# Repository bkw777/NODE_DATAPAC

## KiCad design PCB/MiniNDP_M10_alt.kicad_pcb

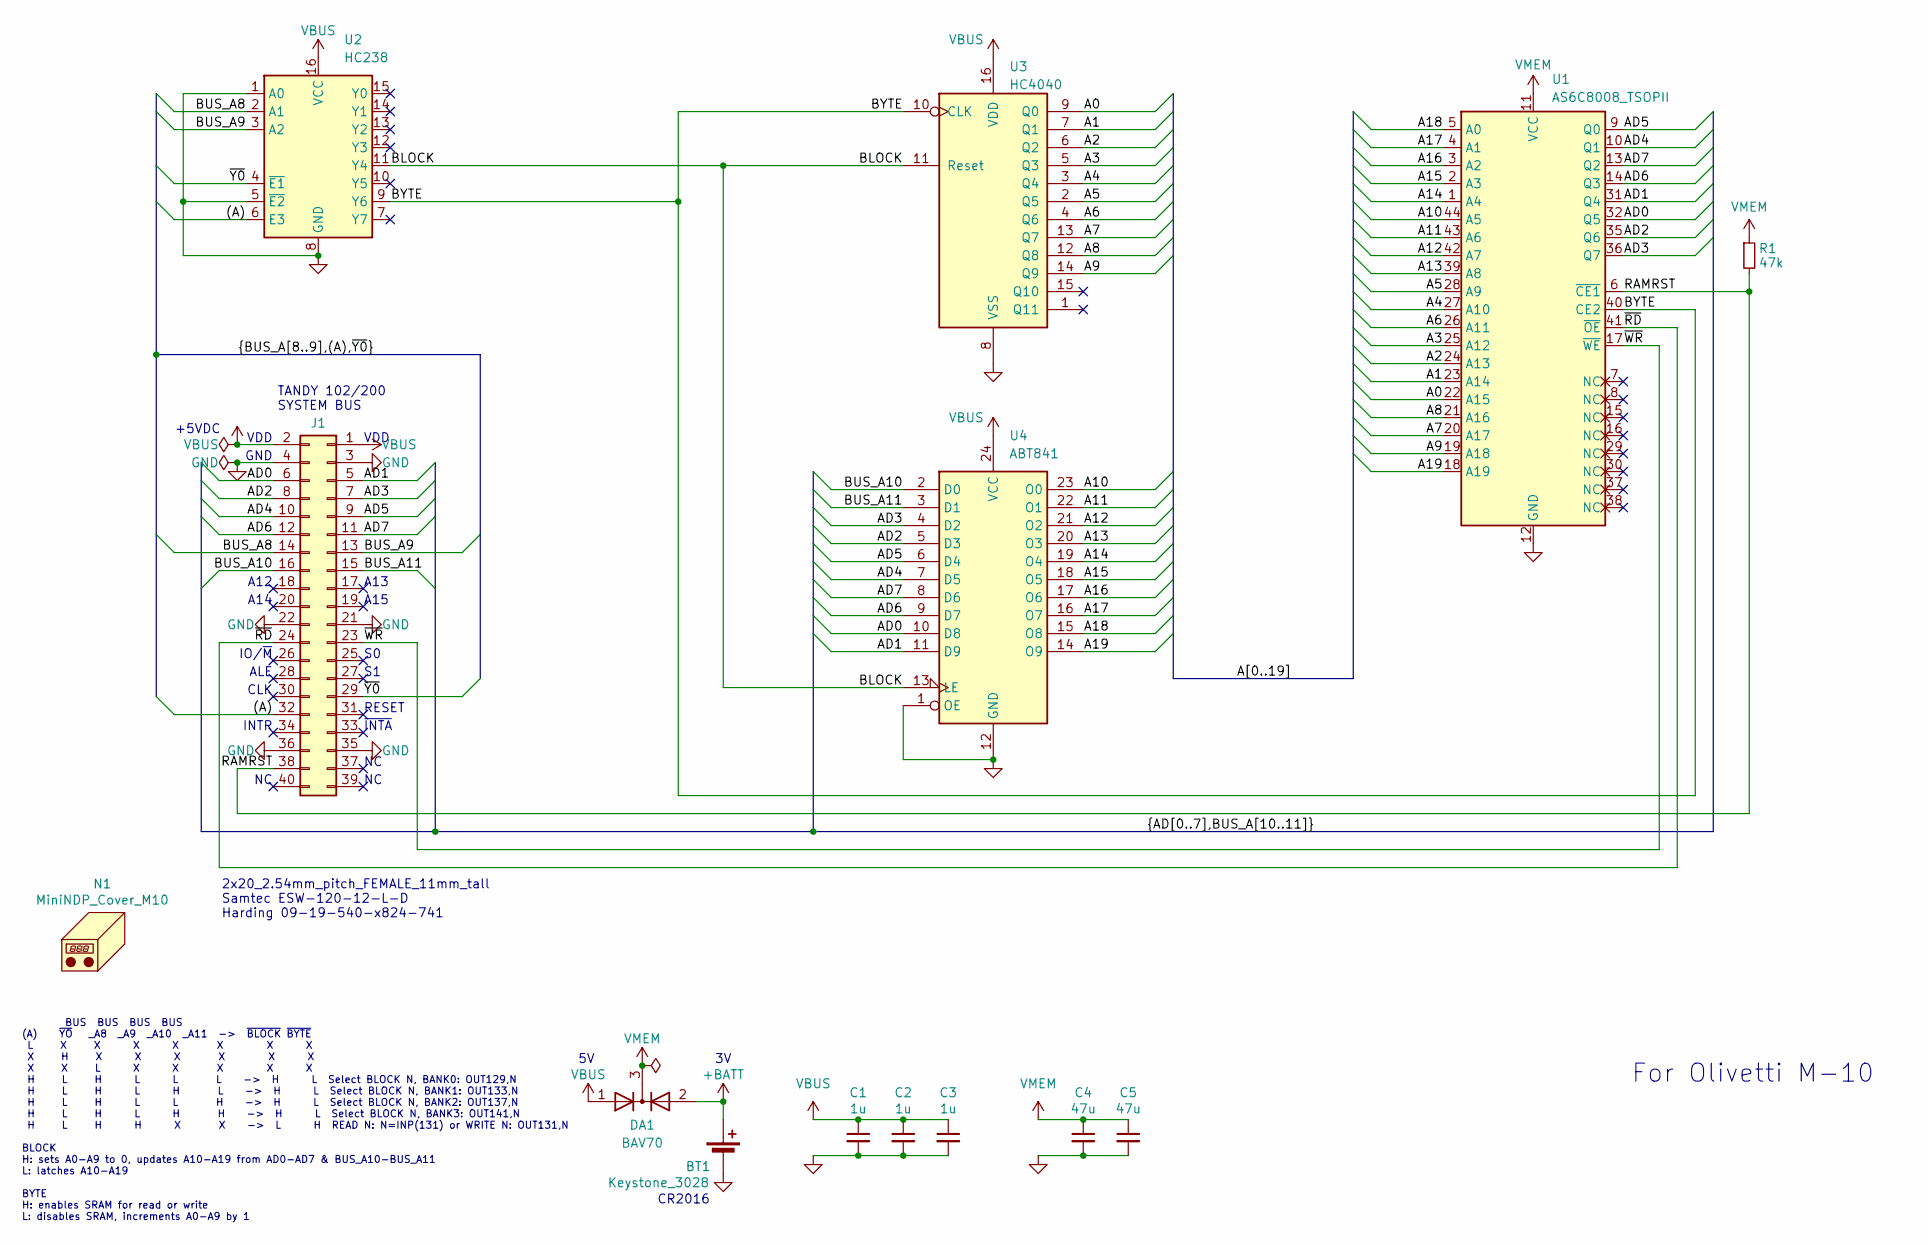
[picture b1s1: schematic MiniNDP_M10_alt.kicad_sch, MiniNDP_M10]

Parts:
BT1: Keystone_3028; Keystone_3028_3034; MPN Keystone 3028
C1, C2, C3: 1u; C_0805; MPN CL21B105KAFNNNE
C4, C5: 47u; C_1206; MPN C3216X5R1E476M160DC
DA1: BAV70; SOT-23; MPN BAV70-7-F
J1: Conn_02x20_Odd_Even; Harding_09-19-540-x824-741; MPN 09195407824741
N1: MiniNDP_Cover_M10; MiniNDP_Cover_THIN; MPN MiniNDP_Cover_THIN.stl
R1: 47k; R_0805; MPN RMCF0805FT47K0
U1: AS6C8008_TSOPII; TSOP-II-44; MPN AS6C8008-55ZIN
U2: HC238; TSSOP-16; MPN 74HC238PW,118
U3: HC4040; TSSOP-16; MPN 74HC4040PW,118
U4: ABT841; TSSOP-24_4.4x7.8mm_P0.65mm; MPN SN74ABT841APW

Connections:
+BATT: BT1.1 (+), DA1.2 (A)
/(A): J1.32, U2.6 (E3)
/A0: U1.22 (A15), U3.9 (Q0)
/A1: U1.23 (A14), U3.7 (Q1)
/A2: U1.24 (A13), U3.6 (Q2)
/A3: U1.25 (A12), U3.5 (Q3)
/A4: U1.27 (A10), U3.3 (Q4)
/A5: U1.28 (A9), U3.2 (Q5)
/A6: U1.26 (A11), U3.4 (Q6)
/A7: U1.20 (A17), U3.13 (Q7)
/A8: U1.21 (A16), U3.12 (Q8)
/A9: U1.19 (A18), U3.14 (Q9)
/A10: U1.44 (A5), U4.23 (O0)
/A11: U1.43 (A6), U4.22 (O1)
/A12: U1.42 (A7), U4.21 (O2)
/A13: U1.39 (A8), U4.20 (O3)
/A14: U1.1 (A4), U4.19 (O4)
/A15: U1.2 (A3), U4.18 (O5)
/A16: U1.3 (A2), U4.17 (O6)
/A17: U1.4 (A1), U4.16 (O7)
/A18: U1.5 (A0), U4.15 (O8)
/A19: U1.18 (A19), U4.14 (O9)
/AD0: J1.6, U1.32 (Q5), U4.10 (D8)
/AD1: J1.5, U1.31 (Q4), U4.11 (D9)
/AD2: J1.8, U1.35 (Q6), U4.5 (D3)
/AD3: J1.7, U1.36 (Q7), U4.4 (D2)
/AD4: J1.10, U1.10 (Q1), U4.7 (D5)
/AD5: J1.9, U1.9 (Q0), U4.6 (D4)
/AD6: J1.12, U1.14 (Q3), U4.9 (D7)
/AD7: J1.11, U1.13 (Q2), U4.8 (D6)
/BLOCK: U2.11 (Y4), U3.11 (Reset), U4.13 (LE)
/BUS_A8: J1.14, U2.2 (A1)
/BUS_A9: J1.13, U2.3 (A2)
/BUS_A10: J1.16, U4.2 (D0)
/BUS_A11: J1.15, U4.3 (D1)
/BYTE: U1.40 (CE2), U2.9 (Y6), U3.10 (CLK)
/RAMRST: J1.38, R1.2, U1.6 (~CE1)
/~RD: J1.24, U1.41 (~OE)
/~WR: J1.23, U1.17 (~WE)
/~Y0: J1.29, U2.4 (~E1)
GND: BT1.2 (-), C1.2, C2.2, C3.2, C4.2, C5.2, J1.3, J1.4, J1.21, J1.22, J1.35, J1.36, U1.12 (GND), U1.34 (GND), U2.1 (A0), U2.5 (~E2), U2.8 (GND), U3.8 (VSS), U4.1 (OE), U4.12 (GND)
VBUS: C1.1, C2.1, C3.1, DA1.1 (A), J1.1, J1.2, U2.16 (VCC), U3.16 (VDD), U4.24 (VCC)
VMEM: C4.1, C5.1, DA1.3 (K), R1.1, U1.11 (VCC), U1.33 (VCC)

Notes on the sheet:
TANDY 102/200 SYSTEM BUS
+5VDC
A15
CR2016
INTR
A14
ALE
~{INTA}
CLK
GND
IO/~{M}
VDD
BUS BUS BUS BUS (A) ~{YO} _A8 _A9 _A10 _A11 -> ~{BLOCK} ~{BYTE} L X X X X X X X X H X X X X X X X X L X X X X X H L H L L L -> H L Select BLOCK N, BANK0: OUT129,N H L H L H L -> H L Select BLOCK N, BANK1: OUT133,N H L H L L H -> H L Select BLOCK N, BANK2: OUT137,N H L H L H H -> H L Select BLOCK N,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
2x20_2.54mm_pitch_FEMALE_11mm_tall Samtec ESW-120-12-L-D Harding 09-19-540-x824-741
RESET
A13
A12
For Olivetti M-10

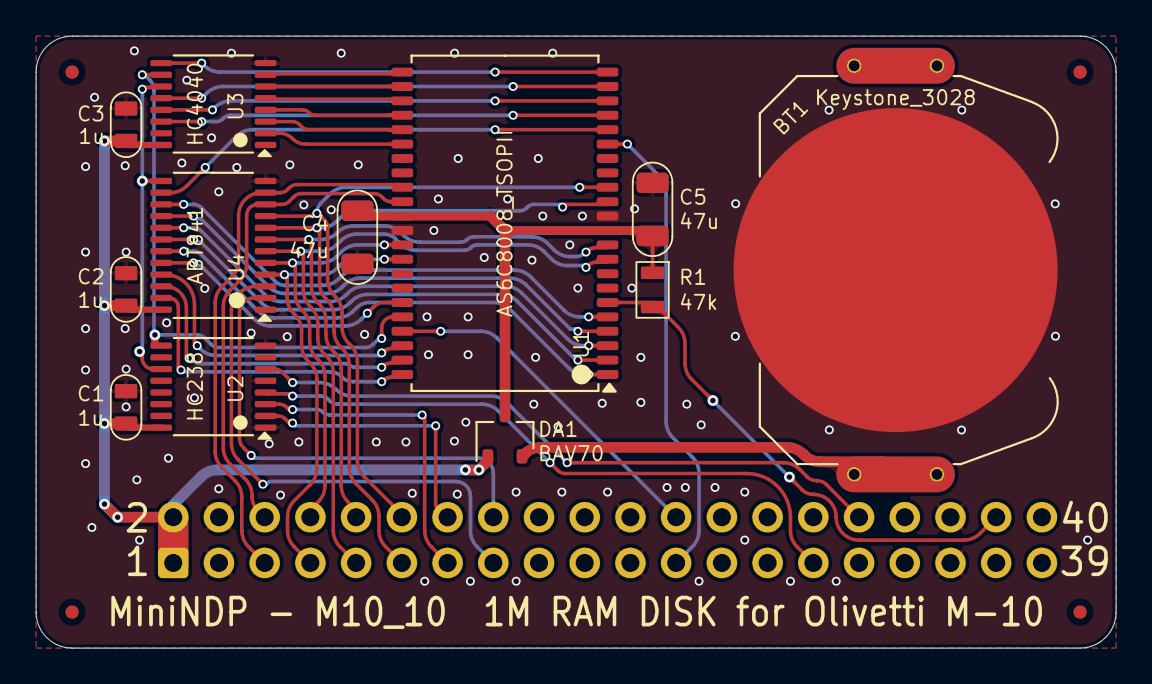
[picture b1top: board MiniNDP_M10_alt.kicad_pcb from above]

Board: 2 copper layers, 60.0 x 34.0 mm, 18 parts (1 on the bottom side), 43 nets.

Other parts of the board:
F3, F3#2, F3#3, F3#4: Fiducial_0.75_1.5

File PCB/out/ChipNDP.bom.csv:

"Reference","Value","Datasheet","Footprint","Qty","DNP","MPN","Description"
"BT1","Keystone_3031","datasheet/Keystone_3031.pdf","000_LOCAL:Keystone_3031","1","","Keystone 3031","Battery Retainer Coin, 10.0mm 1 Cell PC Pin"
"C1,C2,C3","1u","datasheets/CL21B105KAFNNNE.pdf","000_LOCAL:C_0805","3","","CL21B105KAFNNNE","CAP CER 1UF 25V X7R 0805"
"C4","47u","datasheets/TDK_MLCC_Cxxxx.pdf","000_LOCAL:C_1206","1","","C3216X5R1E476M160DC","CAP CER 47UF 25V X5R 1206"
"DA1","BAV70","datasheets/BAV70.pdf","000_LOCAL:SOT-23","1","","BAV70-7-F","DIODE ARRAY GP 75V 150MA SOT23-3"
"J1","Model_100_System_BUS","datasheets/TRS-80_Model_100_User_Guide.pdf","000_LOCAL:DIP-40_PCB","1","","920-0172-01","CONN HEADER VERT 40P 2.54MM"
"R1","47k","datasheets/sei-rmcf_rmcp.pdf","000_LOCAL:R_0805","1","","RMCF0805FT47K0","RES 47K OHM 1% 1/8W 0805"
"U1","AS6C8008_TSOPII","datasheets/AS6C8008.pdf","000_LOCAL:TSOP-II-44","1","","AS6C8008-55ZIN","IC SRAM 1Mx8 PARALLEL 5v TSOP-II-44"
"U2","HC238","datasheets/HC238.pdf","000_LOCAL:TSSOP-16","1","","74HC238PW,118","IC DECODER/DEMUX 1 X 3:8 16SO"
"U3","HC4040","datasheets/4040.pdf","000_LOCAL:TSSOP-16","1","","74HC4040PW,118","IC BINARY COUNTER 12-BIT 16SO"
"U4","ABT841","datasheets/sn54abt841.pdf","000_LOCAL:TSSOP-24_4.4x7.8mm_P0.65mm","1","","SN74ABT841APW","IC 10BIT LATCH 3-STATE 24-SOIC"

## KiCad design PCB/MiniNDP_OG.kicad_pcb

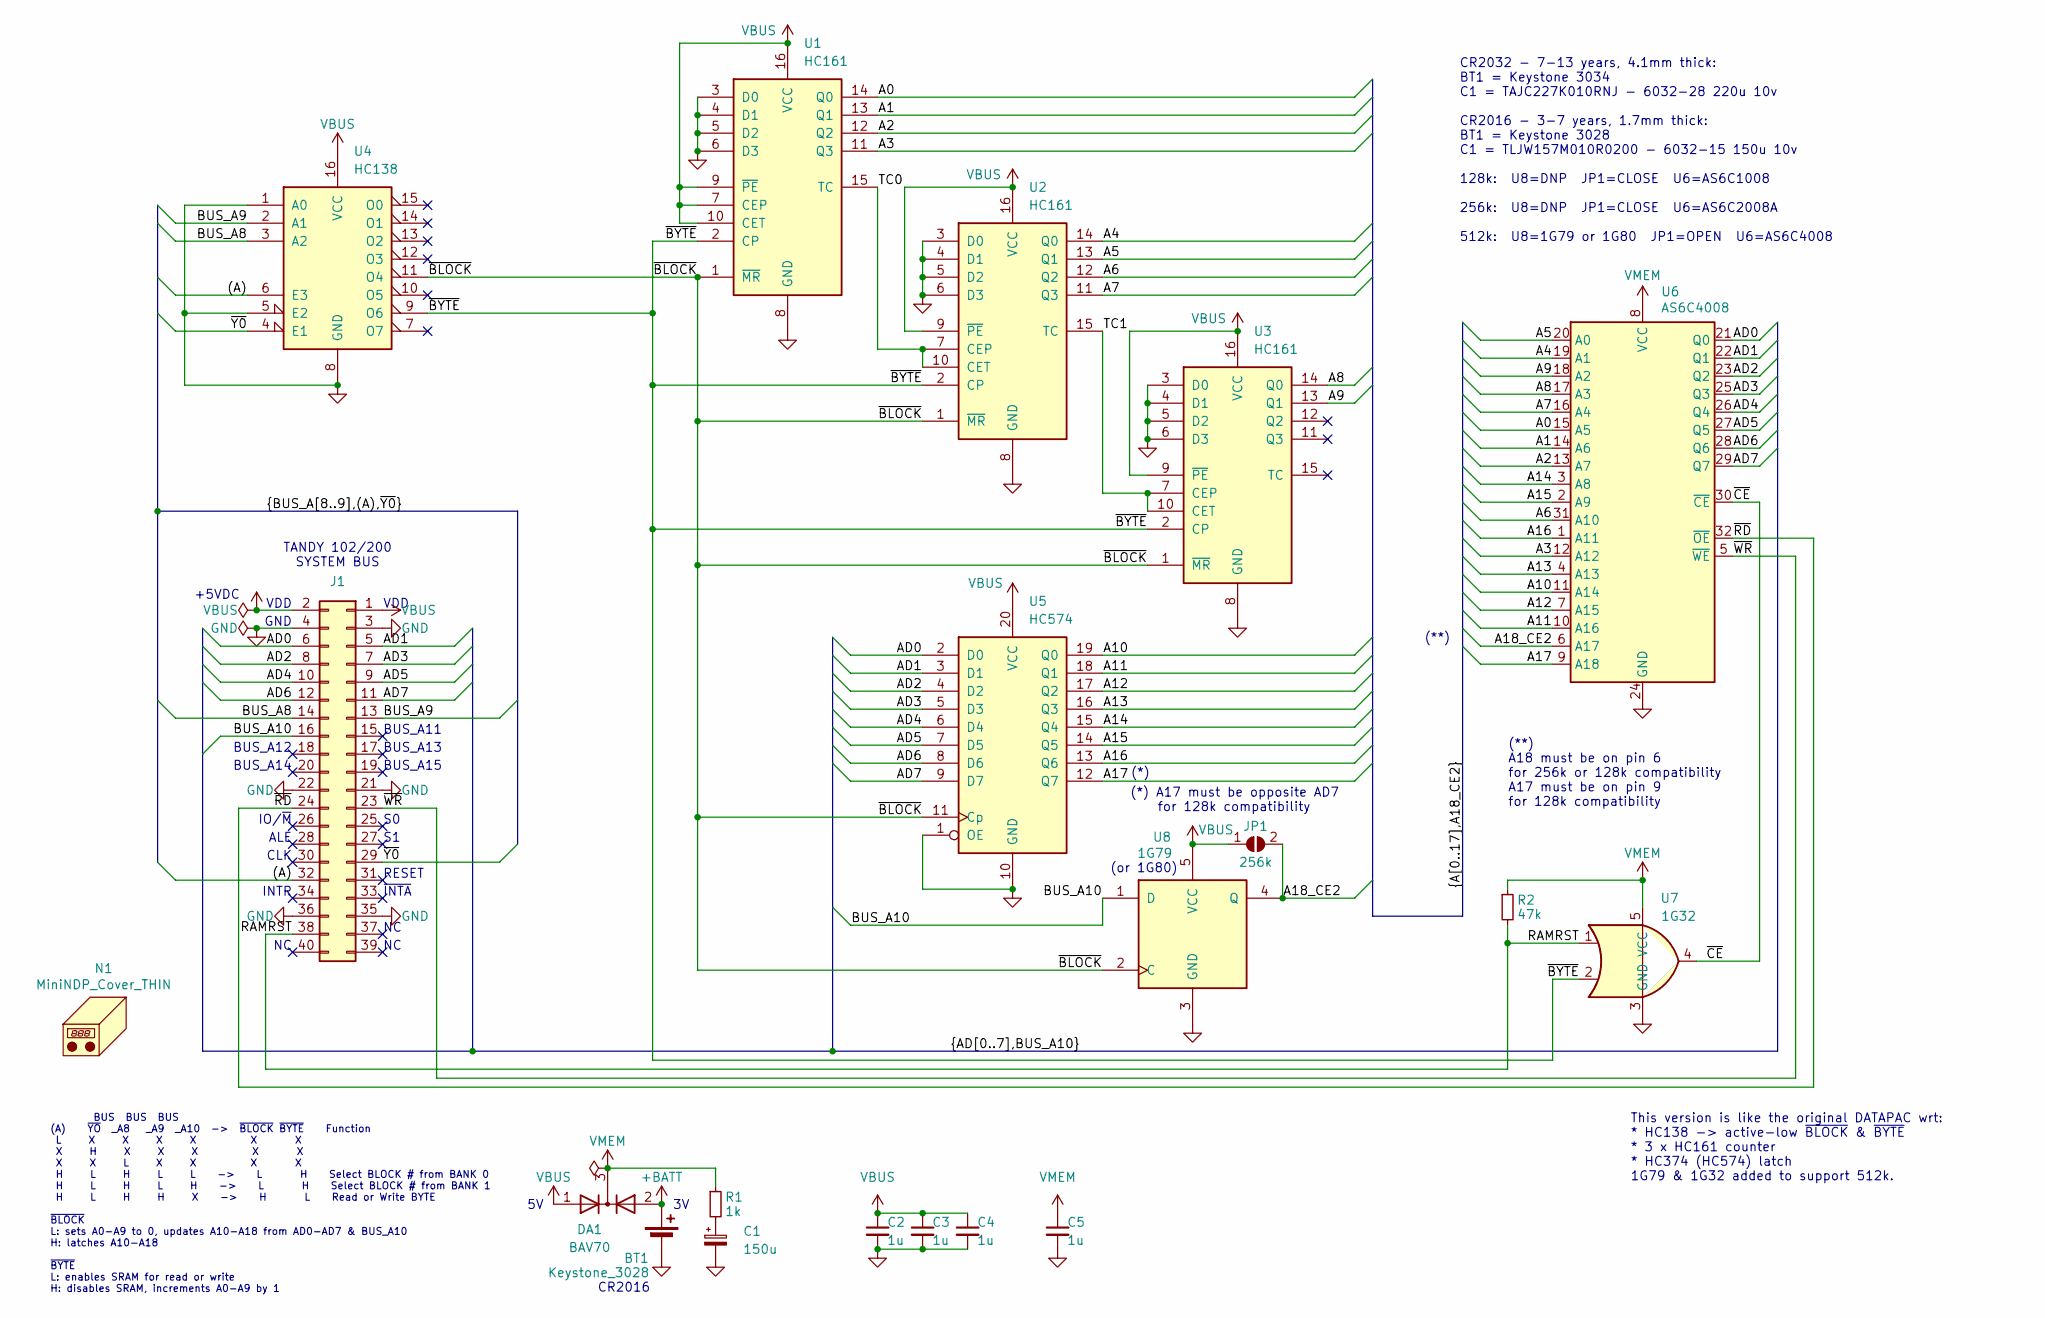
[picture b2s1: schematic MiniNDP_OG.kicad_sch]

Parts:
BT1: Keystone_3028; Keystone_3028_3034; MPN Keystone_3028
C1: 150u; CP_6032; MPN TLJW157M010R0200
C2, C3, C4, C5: 1u; C_0805; MPN CL21B105KAFNNNE
DA1: BAV70; SOT-23; MPN BAV70-7-F
J1: Conn_02x20_Odd_Even; IDC-Header_2x20_P2.54mm_Vertical; MPN 302-S401
JP1: 256k; SolderJumper-2_Open 0.65mm
N1: MiniNDP_Cover_THIN; MPN MiniNDP_Cover_THIN.stl
R1: 1k; R_0805; MPN RK73B2ATTD102J
R2: 47k; R_0805; MPN RMCF0805FT47K0
U1, U2, U3: HC161; TSSOP-16; MPN 74HC161PW,118
U4: HC138; TSSOP-16; MPN 74HC138PW,118
U5: HC574; TSSOP-20; MPN 74HC574PW,118
U6: AS6C4008; TSOP32-dual; MPN AS6C4008-55STIN
U7: 1G32; SOT-353_SC-70-5; MPN 74LVC1G32GW,125
U8: 1G79; SOT-353_SC-70-5; MPN 74LVC1G79GW,125

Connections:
+BATT: BT1.1 (+), DA1.2 (A)
/(A): J1.32, U4.6 (E3)
/A0: U1.14 (Q0), U6.15 (A5)
/A1: U1.13 (Q1), U6.14 (A6)
/A2: U1.12 (Q2), U6.13 (A7)
/A3: U1.11 (Q3), U6.12 (A12)
/A4: U2.14 (Q0), U6.19 (A1)
/A5: U2.13 (Q1), U6.20 (A0)
/A6: U2.12 (Q2), U6.31 (A10)
/A7: U2.11 (Q3), U6.16 (A4)
/A8: U3.14 (Q0), U6.17 (A3)
/A9: U3.13 (Q1), U6.18 (A2)
/A10: U5.19 (Q0), U6.11 (A14)
/A11: U5.18 (Q1), U6.10 (A16)
/A12: U5.17 (Q2), U6.7 (A15)
/A13: U5.16 (Q3), U6.4 (A13)
/A14: U5.15 (Q4), U6.3 (A8)
/A15: U5.14 (Q5), U6.2 (A9)
/A16: U5.13 (Q6), U6.1 (A11)
/A17: U5.12 (Q7), U6.9 (A18)
/A18_CE2: JP1.2 (B), U6.6 (A17), U8.4 (Q)
/AD0: J1.6, U5.2 (D0), U6.21 (Q0)
/AD1: J1.5, U5.3 (D1), U6.22 (Q1)
/AD2: J1.8, U5.4 (D2), U6.23 (Q2)
/AD3: J1.7, U5.5 (D3), U6.25 (Q3)
/AD4: J1.10, U5.6 (D4), U6.26 (Q4)
/AD5: J1.9, U5.7 (D5), U6.27 (Q5)
/AD6: J1.12, U5.8 (D6), U6.28 (Q6)
/AD7: J1.11, U5.9 (D7), U6.29 (Q7)
/BUS_A8: J1.14, U4.3 (A2)
/BUS_A9: J1.13, U4.2 (A1)
/BUS_A10: J1.16, U8.1 (D)
/RAMRST: J1.38, R2.2, U7.1
/TC0: U1.15 (TC), U2.7 (CEP), U2.10 (CET)
/TC1: U2.15 (TC), U3.7 (CEP), U3.10 (CET)
/~BLOCK: U1.1 (~MR), U2.1 (~MR), U3.1 (~MR), U4.11 (O4), U5.11 (Cp), U8.2 (C)
/~BYTE: U1.2 (CP), U2.2 (CP), U3.2 (CP), U4.9 (O6), U7.2
/~CE: U6.30 (~CE), U7.4
/~RD: J1.24, U6.32 (~OE)
/~WR: J1.23, U6.5 (~WE)
/~Y0: J1.29, U4.4 (E1)
GND: BT1.2 (-), C1.2, C2.2, C3.2, C4.2, C5.2, J1.3, J1.4, J1.21, J1.22, J1.35, J1.36, U1.3 (D0), U1.4 (D1), U1.5 (D2), U1.6 (D3), U1.8 (GND), U2.3 (D0), U2.4 (D1), U2.5 (D2), U2.6 (D3), U2.8 (GND), U3.3 (D0), U3.4 (D1), U3.5 (D2), U3.6 (D3), U3.8 (GND), U4.1 (A0), U4.5 (E2), U4.8 (GND), U5.1 (OE), U5.10 (GND), U6.24 (GND), U7.3 (GND), U8.3 (GND)
unnamed: C1.1, R1.2
VBUS: C2.1, C3.1, C4.1, DA1.1 (A), J1.1, J1.2, JP1.1 (A), U1.7 (CEP), U1.9 (~PE), U1.10 (CET), U1.16 (VCC), U2.9 (~PE), U2.16 (VCC), U3.9 (~PE), U3.16 (VCC), U4.16 (VCC), U5.20 (VCC), U8.5 (VCC)
VMEM: C5.1, DA1.3 (K), R1.1, R2.1, U6.8 (VCC), U7.5 (VCC)

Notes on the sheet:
TANDY 102/200 SYSTEM BUS
+5VDC
BUS_A15
INTR
BUS_A14
ALE
~{INTA}
CLK
(**) A18 must be on pin 6 for 256k or 128k compatibility A17 must be on pin 9 for 128k compatibility
CR2032 - 7-13 years, 4.1mm thick: BT1 = Keystone 3034 C1 = TAJC227K010RNJ - 6032-28 220u 10v CR2016 - 3-7 years, 1.7mm thick: BT1 = Keystone 3028 C1 = TLJW157M010R0200 - 6032-15 150u 10v 128k: U8=DNP JP1=CLOSE U6=AS6C1008 256k: U8=DNP JP1=CLOSE U6=AS6C2008A 512k: U8=1G79 or 1G80 JP1=OPEN U6=AS6C4008
GND
IO/~{M}
CR2016
(or 1G80)
VDD
BUS BUS BUS (A) ~{YO} _A8 _A9 _A10 -> ~{BLOCK} ~{BYTE} Function L X X X X X X X H X X X X X X X L X X X X H L H L L -> L H Select BLOCK # from BANK 0 H L H L H -> L H Select BLOCK # from BANK 1 H L H H X -> H L Read or Write BYTE ~{BLOCK} L: sets A0-A9 to 0, updates A10-A18 from AD0-AD7 & BUS_A10 H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
RESET
(*) A17 must be opposite AD7 for 128k compatibility
This version is like the original DATAPAC wrt: * HC138 -> active-low ~{BLOCK} & ~{BYTE} * 3 x HC161 counter * HC374 (HC574) latch 1G79 & 1G32 added to support 512k.
(**)
BUS_A11
BUS_A13
(*)
BUS_A12

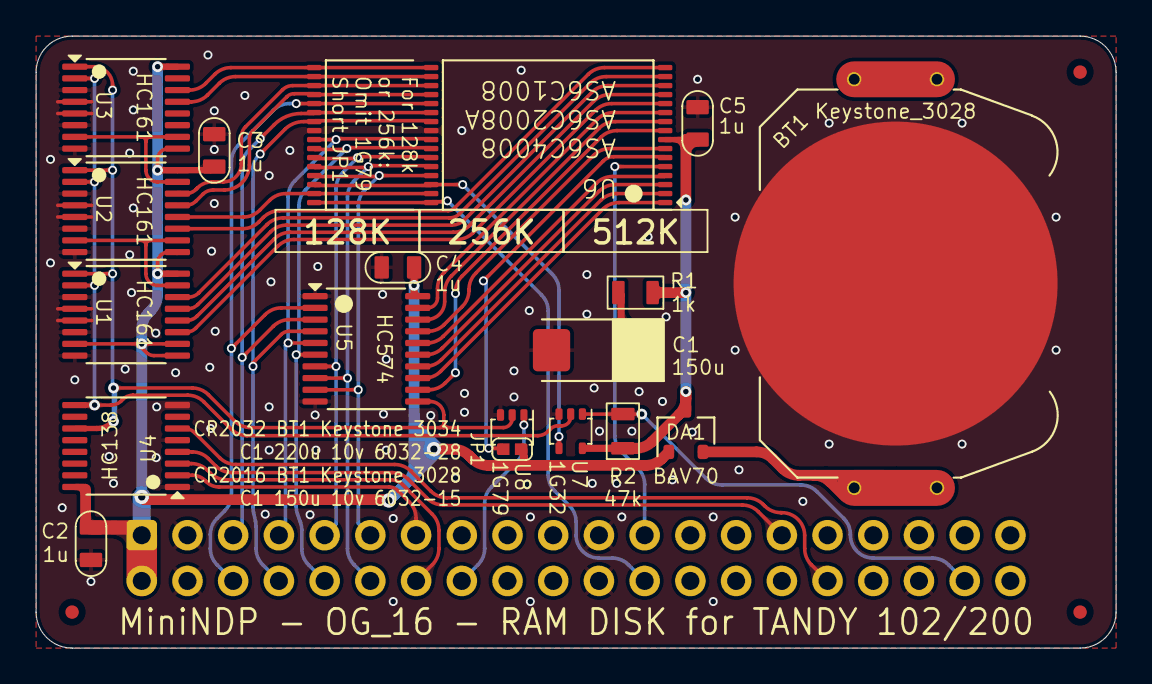
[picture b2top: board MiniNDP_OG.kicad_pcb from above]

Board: 2 copper layers, 60.0 x 34.0 mm, 23 parts (1 on the bottom side), 45 nets.

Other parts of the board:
F3, F3#2, F3#3: Fiducial_0.75_1.5

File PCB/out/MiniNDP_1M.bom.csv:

"Reference","Value","Datasheet","Footprint","Qty","DNP","MPN","Description"
"BT1","Keystone_3034","datasheets/Keystone_3034.pdf","000_LOCAL:Keystone_3028_3034","1","","Keystone 3034","SMT 20mm x 3.2mm coin cell holder"
"C1","220u10v","datasheets/TAJ.odf","000_LOCAL:CP_6032","1","","TAJC227K010RNJ","CAP TANT 220UF 10% 10V 2312"
"C2,C3,C4,C5","1u","datasheets/CL21B105KAFNNNE.pdf","000_LOCAL:C_0805","4","","CL21B105KAFNNNE","CAP CER 1UF 25V X7R 0805"
"DA1","BAS70DW-05","datasheets/BAS70.pdf","000_LOCAL:SOT-363_SC-70-6_symmetric","1","","BAS70DW-05-7-F","DIODE ARR SCHOTT 70V 70MA SOT363 2-PAIR COMMON-CATHODE"
"J1","Conn_02x20_Odd_Even","datasheets/2x20_male_boxed.pdf","000_LOCAL:IDC-Header_2x20_P2.54mm_Vertical","1","","302-S401","CONN HEADER VERT 40POS 2.54MM"
"R1","1k","datasheets/RK73.pdf","000_LOCAL:R_0805","1","","RK73B2ATTD102J","RES 1K OHM 5% 1/4W 0805"
"R2","47k","datasheets/sei-rmcf_rmcp.pdf","000_LOCAL:R_0805","1","","RMCF0805FT47K0","RES 47K OHM 1% 1/8W 0805"
"U1,U2,U3","HC161","datasheets/HC161.pdf","000_LOCAL:TSSOP-16","3","","74HC161PW,118","IC BINARY COUNTER 4-BIT 16TSSOP"
"U4","HC138","datasheets/HC138.pdf","000_LOCAL:TSSOP-16","1","","74HC138PW,118","IC DECODER/DEMUX 1X3:8 16TSSOP"
"U5","FCT821","datasheets/CY74FCT821T.pdf","000_LOCAL:SOIC-24","1","","CY74FCT821BTSOC","IC FF D-TYPE SNGL 10BIT 24SOIC"
"U6","AS6C8008_TSOPII","datasheets/AS6C8008.pdf","000_LOCAL:TSOP-II-44","1","","AS6C8008-55ZIN","IC SRAM 1Mx8 PARALLEL 5v TSOP-II-44"
"U7","1G32","datasheets/LVC1G32.pdf","000_LOCAL:SOT-353_SC-70-5","1","","74LVC1G32GW,125","IC GATE OR 1CH 2-INP 5TSSOP"

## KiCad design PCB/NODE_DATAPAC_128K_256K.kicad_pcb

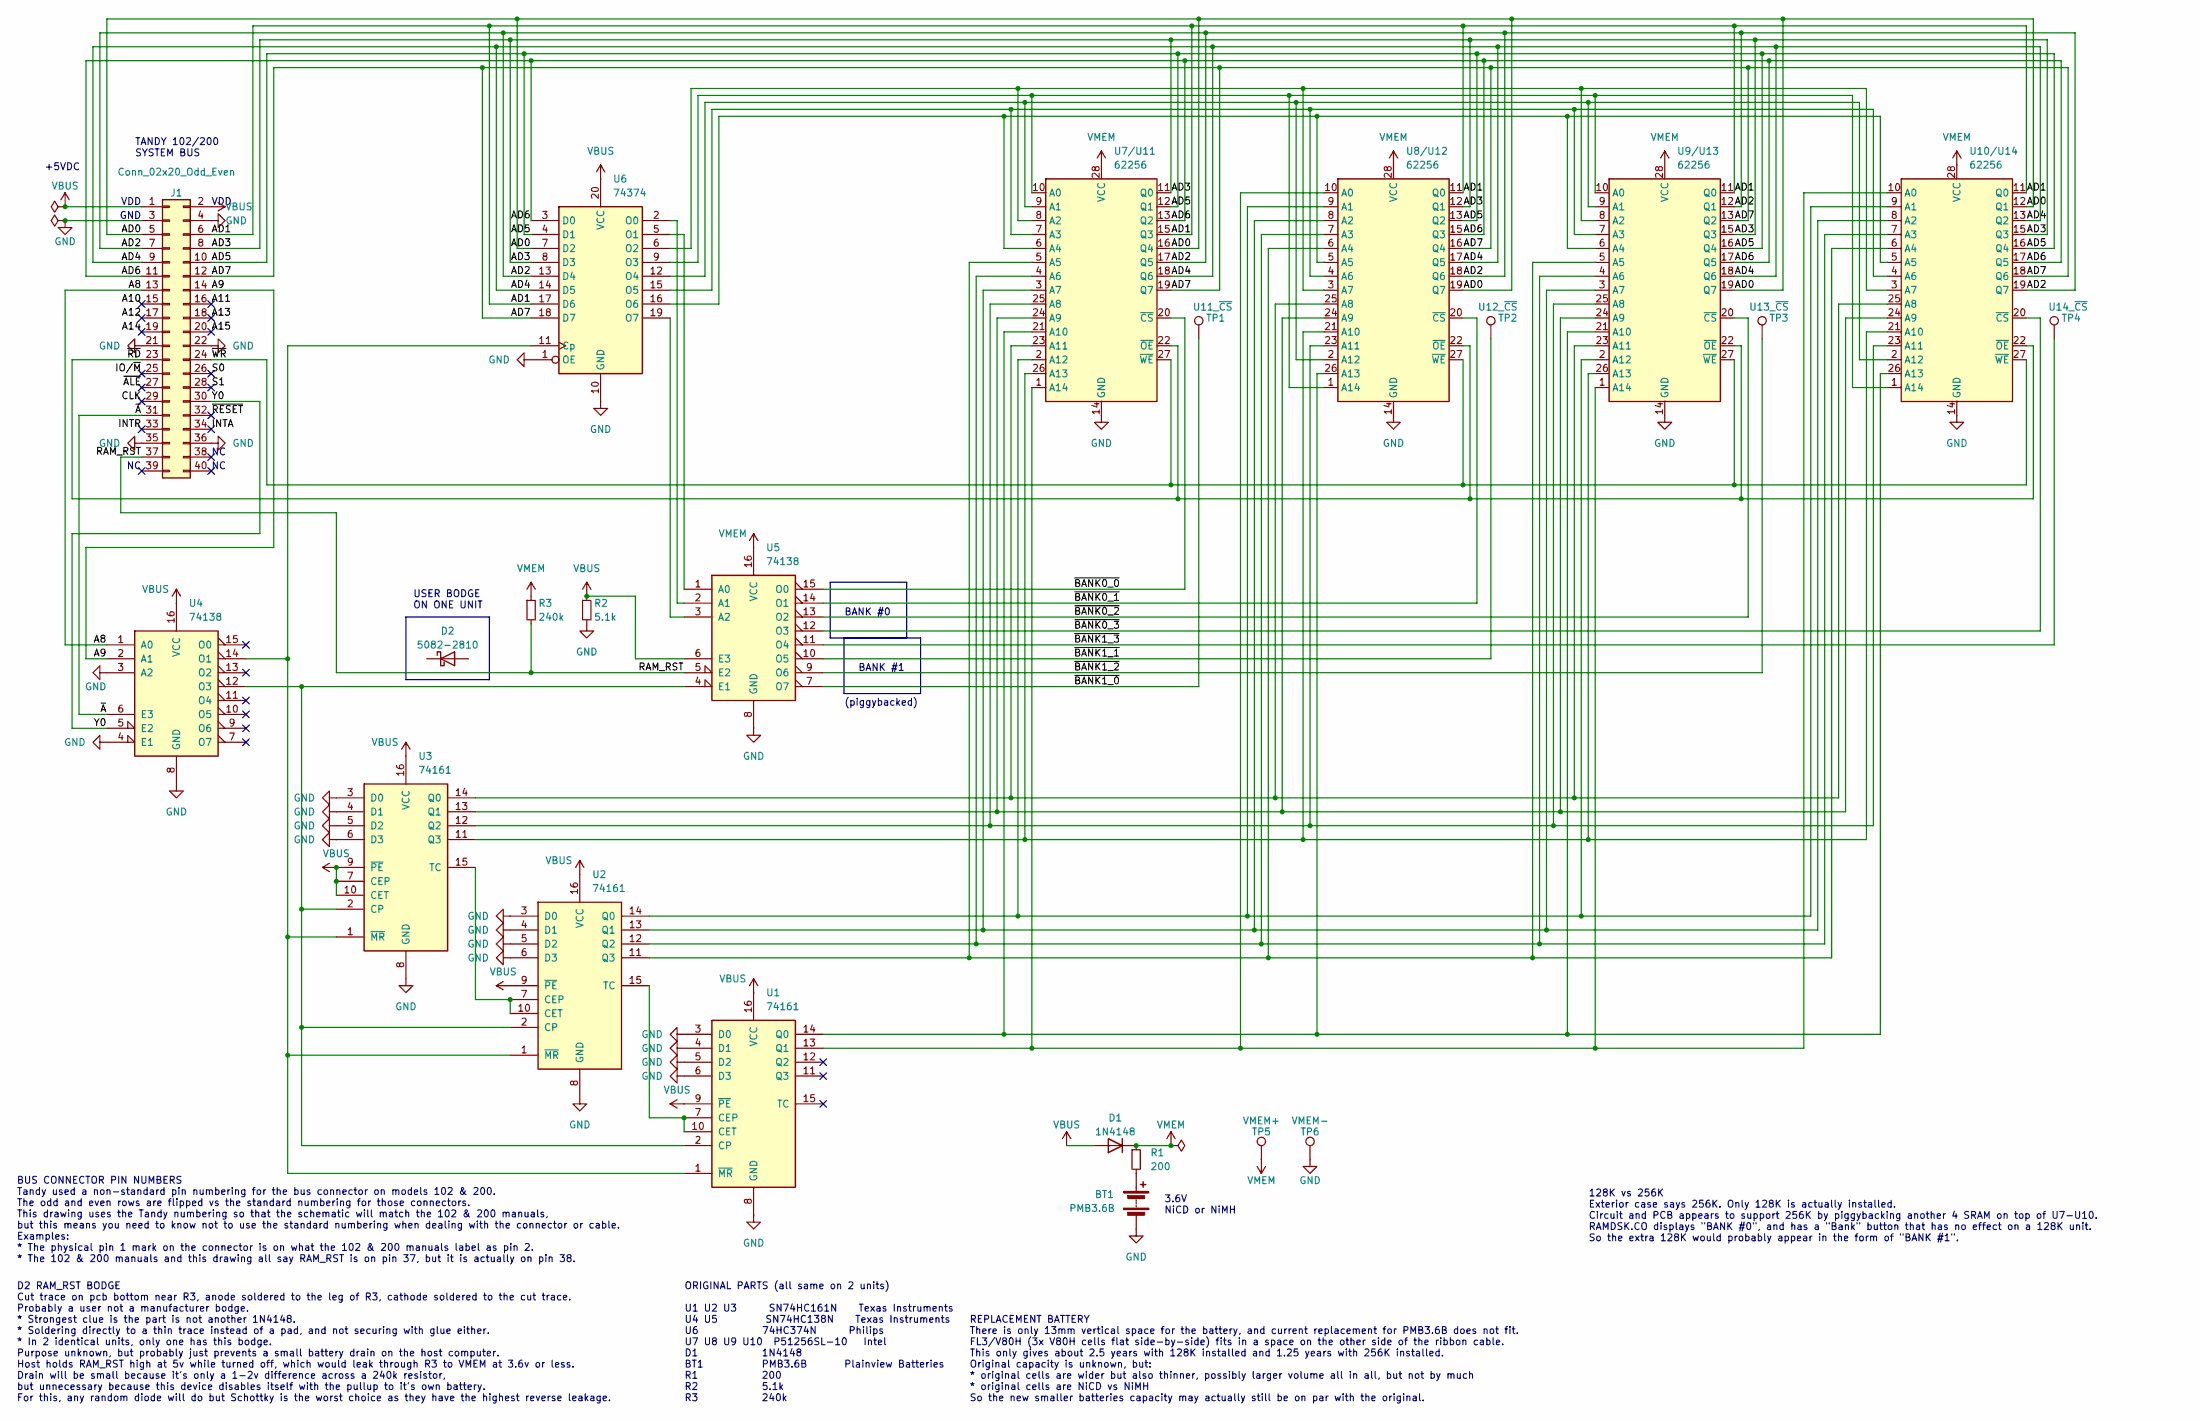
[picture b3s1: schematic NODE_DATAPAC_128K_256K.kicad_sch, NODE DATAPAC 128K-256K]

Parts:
BT1: PMB3.6B
D1: 1N4148; D_DO-35_SOD27_P10.16mm_Horizontal
D2: 5082-2810
J1: Conn_02x20_Odd_Even; IDC_to_board_2x20_flipped
R1: 200; R_Axial_DIN0207_L6.3mm_D2.5mm_P10.16mm_Horizontal
R2: 5.1k; R_Axial_DIN0207_L6.3mm_D2.5mm_P10.16mm_Horizontal
R3: 240k; R_Axial_DIN0207_L6.3mm_D2.5mm_P10.16mm_Horizontal
TP1: U11_~{CS}; TP_THT
TP2: U12_~{CS}; TP_THT
TP3: U13_~{CS}; TP_THT
TP4: U14_~{CS}; TP_THT
TP5: VMEM+; TP_THT_pwr
TP6: VMEM-; TP_THT_pwr
U1, U2, U3: 74161; DIP-16_W7.62mm
U4, U5: 74138; DIP-16_W7.62mm
U6: 74374; DIP-20_W7.62mm
U7/U11, U8/U12, U9/U13, U10/U14: 62256; DIP-28_W15.24mm

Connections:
/A8: J1.13, U4.1 (A0)
/A9: J1.14, U4.2 (A1)
/A10: J1.15
/A11: J1.16
/A12: J1.17
/A13: J1.18
/A14: J1.19
/A15: J1.20
/AD0: J1.5, U6.7 (D2), U7/U11.16 (Q4), U8/U12.19 (Q7), U9/U13.19 (Q7), U10/U14.12 (Q1)
/AD1: J1.6, U6.17 (D6), U7/U11.15 (Q3), U8/U12.11 (Q0), U9/U13.11 (Q0), U10/U14.11 (Q0)
/AD2: J1.7, U6.13 (D4), U7/U11.17 (Q5), U8/U12.18 (Q6), U9/U13.12 (Q1), U10/U14.19 (Q7)
/AD3: J1.8, U6.8 (D3), U7/U11.11 (Q0), U8/U12.12 (Q1), U9/U13.15 (Q3), U10/U14.15 (Q3)
/AD4: J1.9, U6.14 (D5), U7/U11.18 (Q6), U8/U12.17 (Q5), U9/U13.18 (Q6), U10/U14.13 (Q2)
/AD5: J1.10, U6.4 (D1), U7/U11.12 (Q1), U8/U12.13 (Q2), U9/U13.16 (Q4), U10/U14.16 (Q4)
/AD6: J1.11, U6.3 (D0), U7/U11.13 (Q2), U8/U12.15 (Q3), U9/U13.17 (Q5), U10/U14.17 (Q5)
/AD7: J1.12, U6.18 (D7), U7/U11.19 (Q7), U8/U12.16 (Q4), U9/U13.13 (Q2), U10/U14.18 (Q6)
/CLK: J1.29
/INTA: J1.34
/INTR: J1.33
/IO/~M: J1.25
/RAM_RST: J1.37, R3.2, U5.5 (E2)
/S0: J1.26
/S1: J1.28
/Y0: J1.30, U4.5 (E2)
/~ALE: J1.27
/~A: J1.31, U4.6 (E3)
/~BANK0_0: U5.15 (O0), U7/U11.20 (~CS)
/~BANK0_1: U5.14 (O1), U8/U12.20 (~CS)
/~BANK0_2: U5.13 (O2), U9/U13.20 (~CS)
/~BANK0_3: U5.12 (O3), U10/U14.20 (~CS)
/~BANK1_0: TP1.1, U5.7 (O7)
/~BANK1_1: TP2.1, U5.10 (O5)
/~BANK1_2: TP3.1, U5.9 (O6)
/~BANK1_3: TP4.1, U5.11 (O4)
/~RD: J1.23, U7/U11.22 (~OE), U8/U12.22 (~OE), U9/U13.22 (~OE), U10/U14.22 (~OE)
/~RESET: J1.32
/~WR: J1.24, U7/U11.27 (~WE), U8/U12.27 (~WE), U9/U13.27 (~WE), U10/U14.27 (~WE)
GND: BT1.2 (-), J1.3, J1.4, J1.21, J1.22, J1.35, J1.36, R2.2, TP6.1, U1.3 (D0), U1.4 (D1), U1.5 (D2), U1.6 (D3), U1.8 (GND), U2.3 (D0), U2.4 (D1), U2.5 (D2), U2.6 (D3), U2.8 (GND), U3.3 (D0), U3.4 (D1), U3.5 (D2), U3.6 (D3), U3.8 (GND), U4.3 (A2), U4.4 (E1), U4.8 (GND), U5.8 (GND), U6.1 (OE), U6.10 (GND), U7/U11.14 (GND), U8/U12.14 (GND), U9/U13.14 (GND), U10/U14.14 (GND)
unnamed: BT1.1 (+), R1.2
unnamed: U1.7 (CEP), U1.10 (CET), U2.15 (TC)
unnamed: U1.2 (CP), U2.2 (CP), U3.2 (CP), U4.12 (O3), U5.4 (E1)
unnamed: U1.14 (Q0), U7/U11.21 (A10), U8/U12.26 (A13), U9/U13.21 (A10), U10/U14.26 (A13)
unnamed: U1.13 (Q1), U7/U11.1 (A14), U8/U12.10 (A0), U9/U13.1 (A14), U10/U14.10 (A0)
unnamed: U1.1 (~MR), U2.1 (~MR), U3.1 (~MR), U4.14 (O1), U6.11 (Cp)
unnamed: U2.7 (CEP), U2.10 (CET), U3.15 (TC)
unnamed: U5.1 (A0), U6.5 (O1)
unnamed: U5.2 (A1), U6.2 (O0)
unnamed: U5.3 (A2), U6.19 (O7)
unnamed: U2.14 (Q0), U7/U11.2 (A12), U8/U12.9 (A1), U9/U13.2 (A12), U10/U14.9 (A1)
unnamed: U2.13 (Q1), U7/U11.3 (A7), U8/U12.8 (A2), U9/U13.3 (A7), U10/U14.8 (A2)
unnamed: U2.12 (Q2), U7/U11.4 (A6), U8/U12.7 (A3), U9/U13.4 (A6), U10/U14.7 (A3)
unnamed: U2.11 (Q3), U7/U11.5 (A5), U8/U12.6 (A4), U9/U13.5 (A5), U10/U14.6 (A4)
unnamed: U6.16 (O6), U7/U11.6 (A4), U8/U12.5 (A5), U9/U13.6 (A4), U10/U14.5 (A5)
unnamed: U6.15 (O5), U7/U11.7 (A3), U8/U12.4 (A6), U9/U13.7 (A3), U10/U14.4 (A6)
unnamed: U6.6 (O2), U7/U11.8 (A2), U8/U12.3 (A7), U9/U13.8 (A2), U10/U14.3 (A7)
unnamed: U3.14 (Q0), U7/U11.23 (A11), U8/U12.25 (A8), U9/U13.23 (A11), U10/U14.25 (A8)
unnamed: U3.13 (Q1), U7/U11.24 (A9), U8/U12.24 (A9), U9/U13.24 (A9), U10/U14.24 (A9)
unnamed: U3.11 (Q3), U7/U11.26 (A13), U8/U12.21 (A10), U9/U13.26 (A13), U10/U14.21 (A10)
unnamed: U3.12 (Q2), U7/U11.25 (A8), U8/U12.23 (A11), U9/U13.25 (A8), U10/U14.23 (A11)
unnamed: U6.12 (O4), U7/U11.9 (A1), U8/U12.2 (A12), U9/U13.9 (A1), U10/U14.2 (A12)
unnamed: U6.9 (O3), U7/U11.10 (A0), U8/U12.1 (A14), U9/U13.10 (A0), U10/U14.1 (A14)
VBUS: D1.2 (A), J1.1, J1.2, R2.1, U1.9 (~PE), U1.16 (VCC), U2.9 (~PE), U2.16 (VCC), U3.7 (CEP), U3.9 (~PE), U3.10 (CET), U3.16 (VCC), U4.16 (VCC), U5.6 (E3), U6.20 (VCC)
VMEM: D1.1 (K), R1.1, R3.1, TP5.1, U5.16 (VCC), U7/U11.28 (VCC), U8/U12.28 (VCC), U9/U13.28 (VCC), U10/U14.28 (VCC)

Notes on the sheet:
128K vs 256K Exterior case says 256K. Only 128K is actually installed. Circuit and PCB appears to support 256K by piggybacking another 4 SRAM on top of U7-U10. RAMDSK.CO displays "BANK #0", and has a "Bank" button that has no effect on a 128K unit. So the extra 128K would probably appear in the for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
TANDY 102/200 SYSTEM BUS
+5VDC
D2 RAM_RST BODGE Cut trace on pcb bottom near R3, anode soldered to the leg of R3, cathode soldered to the cut trace. Probably a user not a manufacturer bodge. * Strongest clue is the part is not another 1N4148. * Soldering directly to a thin trace instead of a pad, and not securing with glue eithe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
BANK #0
BANK #1
3.6V NiCD or NiMH
USER BODGE ON ONE UNIT
(piggybacked)
GND
BUS CONNECTOR PIN NUMBERS Tandy used a non-standard pin numbering for the bus connector on models 102 & 200. The odd and even rows are flipped vs the standard numbering for those connectors. This drawing uses the Tandy numbering so that the schematic will match the 102 & 200 manuals, but this means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
VDD
REPLACEMENT BATTERY There is only 13mm vertical space for the battery, and current replacement for PMB3.6B does not fit. FL3/V80H (3x V80H cells flat side-by-side) fits in a space on the other side of the ribbon cable. This only gives about 2.5 years with 128K installed and 1.25 years with 256K ins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
ORIGINAL PARTS (all same on 2 units) U1 U2 U3 SN74HC161N Texas Instruments U4 U5 SN74HC138N Texas Instruments U6 74HC374N Philips U7 U8 U9 U10 P51256SL-10 Intel D1 1N4148 BT1 PMB3.6B Plainview Batteries R1 200 R2 5.1k R3 240k

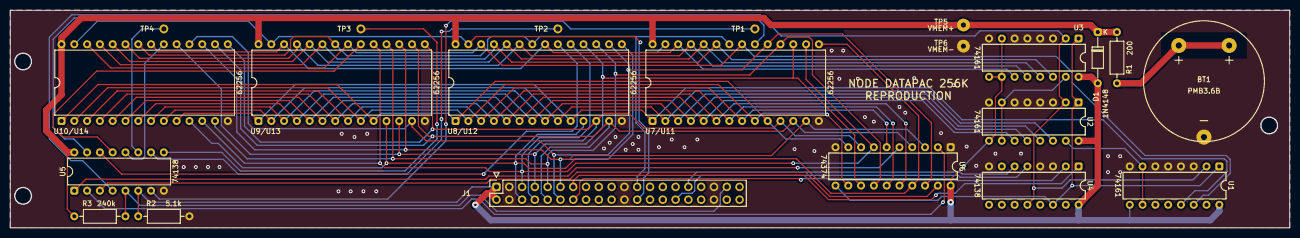
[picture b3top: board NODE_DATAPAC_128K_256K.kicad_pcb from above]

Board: 2 copper layers, 254.0 x 43.2 mm, 22 parts (0 on the bottom side), 49 nets.
